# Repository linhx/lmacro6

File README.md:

# LMACRO6

My custom macropad

## Default keymap

```plaintext
| F20            |            | Mute        |
| Ctrl + F12     | Alt + Left | Alt + Right |
| Ctrl + Alt + T |            |             |

* Left rotary encoder: Switch layer
* Right rotary encoder: Volume up/down

```

### useful macros (config via VIA)

* Open terminal in a directory (Nautilus Ubuntu): {KC_F10}{500}{KC_LALT,KC_E}

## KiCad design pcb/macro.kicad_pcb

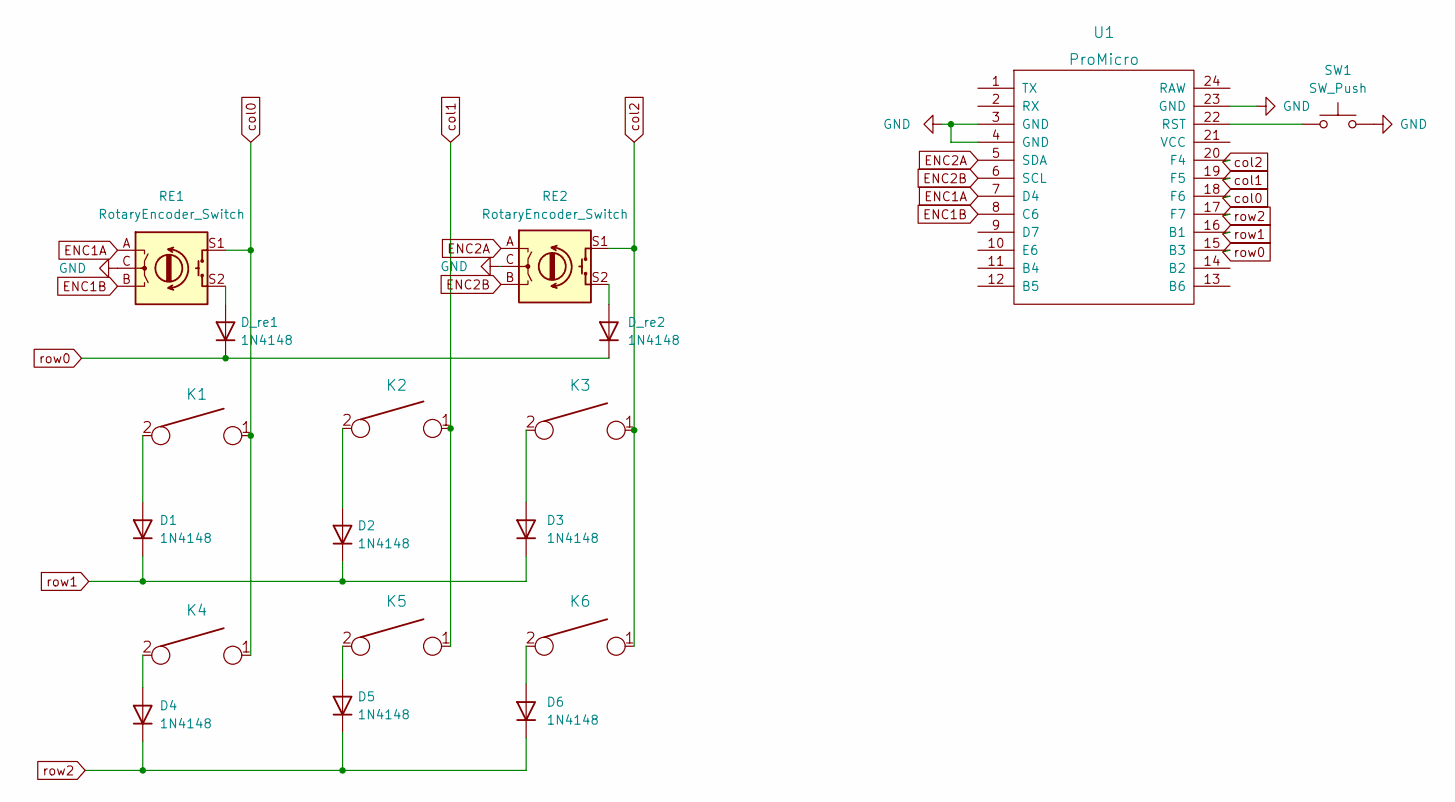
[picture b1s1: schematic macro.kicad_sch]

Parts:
D1, D2, D3, D4, D5, D6: 1N4148; D_DO-35_SOD27_P7.62mm_Horizontal
D_re1, D_re2: 1N4148; D_DO-35_SOD27_P7.62mm_Horizontal
K1, K2, K3, K4, K5, K6: KEYSW; SW_Cherry_MX_PCB_1.00u
RE1, RE2: RotaryEncoder_Switch; RotaryEncoder_Alps_EC11E-Switch_Vertical_H20mm
SW1: SW_Push; SW_SPST_CK_RS282G05A3
U1: ProMicro; Sparkfun_Pro_Micro

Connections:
ENC1A: RE1.A, U1.7 (D4)
ENC1B: RE1.B, U1.8 (C6)
ENC2A: RE2.A, U1.5 (SDA)
ENC2B: RE2.B, U1.6 (SCL)
GND: RE1.C, RE2.C, SW1.2, U1.3 (GND), U1.4 (GND), U1.23 (GND)
unnamed: D1.2 (A), K1.2
unnamed: D2.2 (A), K2.2
unnamed: D3.2 (A), K3.2
unnamed: D4.2 (A), K4.2
unnamed: D5.2 (A), K5.2
unnamed: D6.2 (A), K6.2
unnamed: D_re1.2 (A), RE1.S2
unnamed: D_re2.2 (A), RE2.S2
unnamed: SW1.1, U1.22 (RST)
col0: K1.1, K4.1, RE1.S1, U1.18 (F6)
col1: K2.1, K5.1, U1.19 (F5)
col2: K3.1, K6.1, RE2.S1, U1.20 (F4)
row0: D_re1.1 (K), D_re2.1 (K), U1.15 (B3)
row1: D1.1 (K), D2.1 (K), D3.1 (K), U1.16 (B1)
row2: D4.1 (K), D5.1 (K), D6.1 (K), U1.17 (F7)

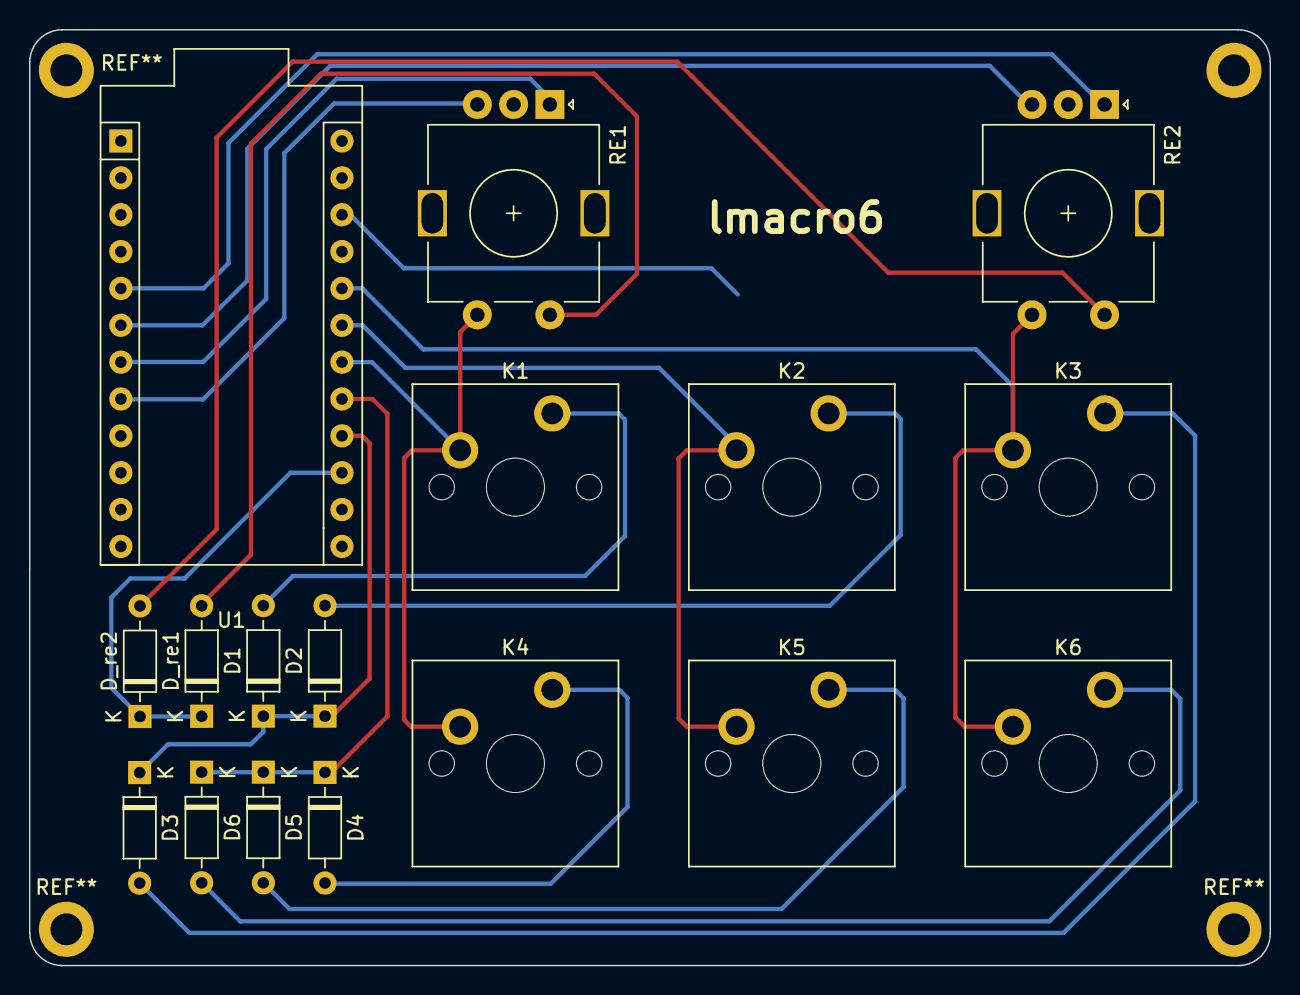
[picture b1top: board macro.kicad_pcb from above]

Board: 2 copper layers, 85.5 x 64.5 mm, 18 parts (1 on the bottom side), 20 nets.

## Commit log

2023-02-12 feat: add PCB design; add testing firmware (tested on ProMicro)
2023-02-12 generate Gerber file
2023-02-12 feat: update clearance to 0.5mm
2023-02-13 feat: add button switch for reset
2023-02-25 feat: update default layout + via support
2023-02-26 fix: align rotary encoders.
2023-02-26 chore: add README.md
2023-02-27 chore: generate plots
2023-03-03 chore: update README
2023-03-24 feat: add 2 more layers, use TX/RX led as Layer indicator
